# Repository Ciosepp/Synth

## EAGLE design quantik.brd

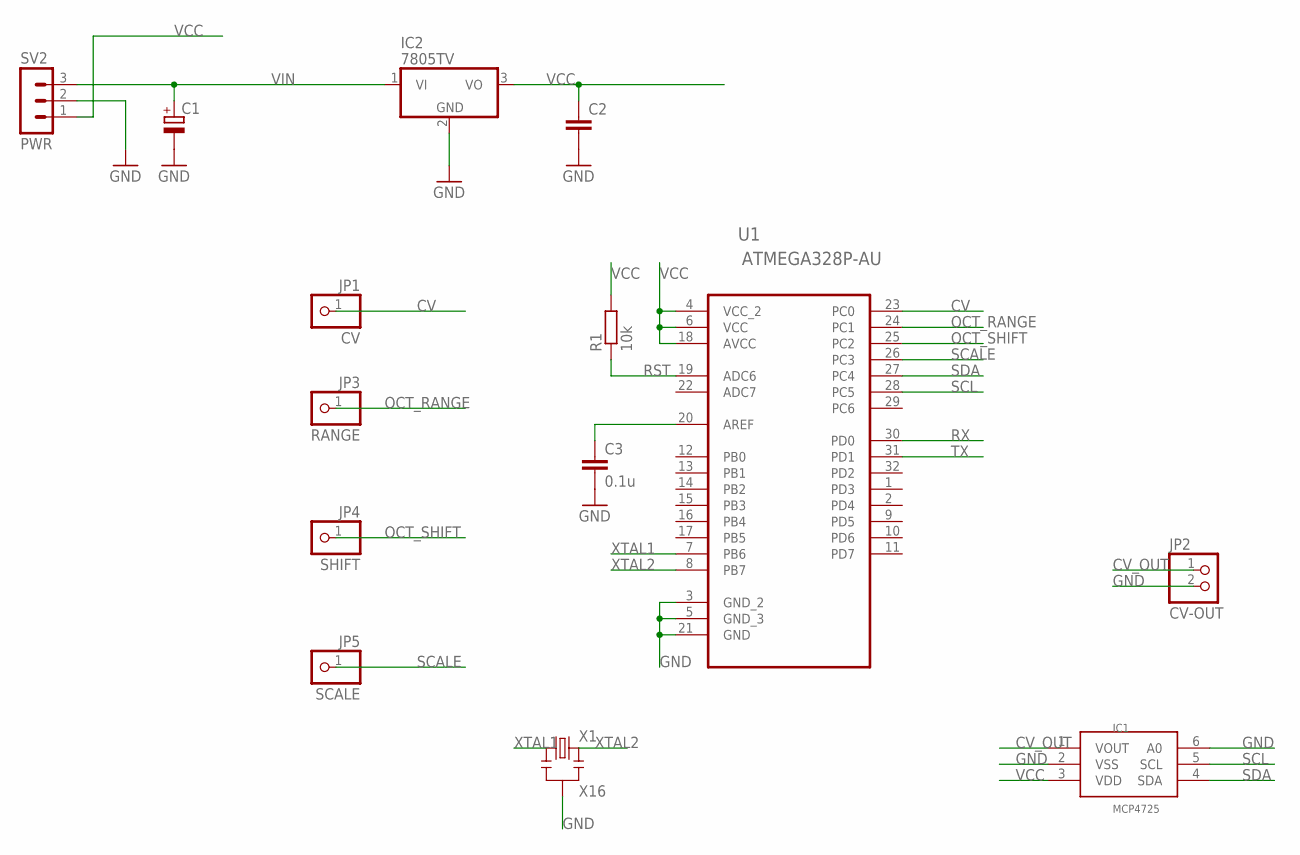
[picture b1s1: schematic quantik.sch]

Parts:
C1: CPOL-EUE5-10.5; E5-10,5
C2: C-EU050-030X075; C050-030X075
C3: 0.1u; C0805
IC1: MCP4725; SOT23-6
IC2: 7805TV; TO220V
JP1: CV; 1X01
JP2: CV-OUT; 1X02
JP3: RANGE; 1X01
JP4: SHIFT; 1X01
JP5: SCALE; 1X01
R1: 10k; R0805
SV2: PWR; MA03-1
U1: ATMEGA328P-AU; QFP80P900X900X120-32N
X1: X16; RESONATOR_SMD

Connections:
CV: JP1.1, U1.23 (PC0)
CV_OUT: IC1.1 (VOUT), JP2.1
GND: C1.-, C2.2, C3.2, IC1.2 (VSS), IC1.6 (A0), IC2.2 (GND), JP2.2, SV2.2, U1.3 (GND_2), U1.5 (GND_3), U1.21 (GND), X1.2
unnamed: C3.1, U1.20 (AREF)
OCT_RANGE: JP3.1, U1.24 (PC1)
OCT_SHIFT: JP4.1, U1.25 (PC2)
RST: R1.1, U1.19 (ADC6)
RX: U1.30 (PD0)
SCALE: JP5.1, U1.26 (PC3)
SCL: IC1.5 (SCL), U1.28 (PC5)
SDA: IC1.4 (SDA), U1.27 (PC4)
TX: U1.31 (PD1)
VCC: C2.1, IC1.3 (VDD), IC2.3 (VO), R1.2, SV2.1, U1.4 (VCC_2), U1.6 (VCC), U1.18 (AVCC)
VIN: C1.+, IC2.1 (VI), SV2.3
XTAL1: U1.7 (PB6), X1.1
XTAL2: U1.8 (PB7), X1.3

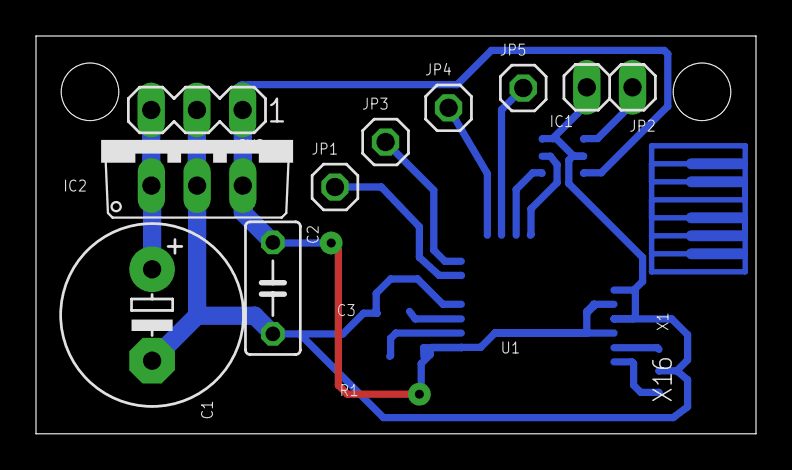
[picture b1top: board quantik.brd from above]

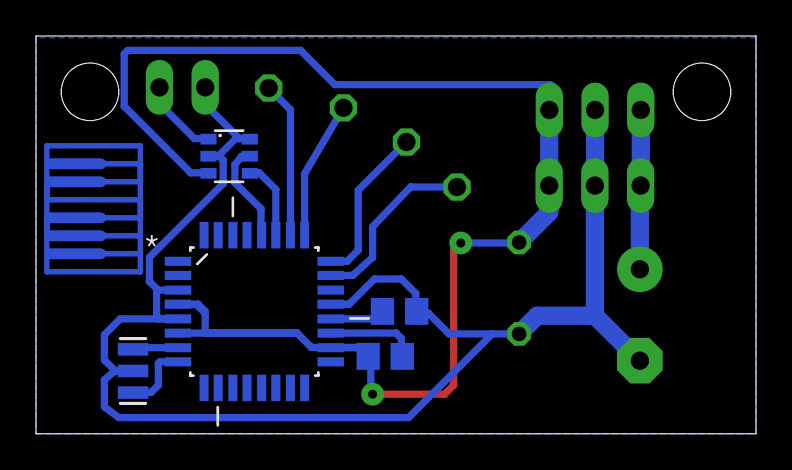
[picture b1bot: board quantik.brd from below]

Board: 2 copper layers, 40.0 x 22.1 mm, 14 parts (5 on the bottom side), 14 nets.

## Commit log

2021-10-22 Add files via upload
    begin
